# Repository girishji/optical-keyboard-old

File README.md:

# optical-keyboard

Keyboard PCB for Gateron optical switches (KiCad project).

- See [Optical Keyboard Design](https://girishji.github.io/jekyll/update/2022/08/17/optical-keyboard-design.html)
- There is a python script that is used for placing switches and laying out
  tracks. See also [KiCad 6 Python Scripting](https://girishji.github.io/)
- [QMK](https://github.com/girishji/qmk_firmware/tree/giri-optical-matrix/keyboards/opticalkb) code for this keyboard
- There is KiCad project for switch cutout plate under `switch-coutout` directory
- Part numbers for JLCPCB are embedded into symbols
- There is also a [single switch PCB](https://github.com/girishji/optical-amoeba)
- Another optical [keyboard](https://github.com/Dachtire/sok42) that might interest you
- Blackpill reference, including [pins to avoid](https://docs.qmk.fm/#/platformdev_blackpill_f411)

***

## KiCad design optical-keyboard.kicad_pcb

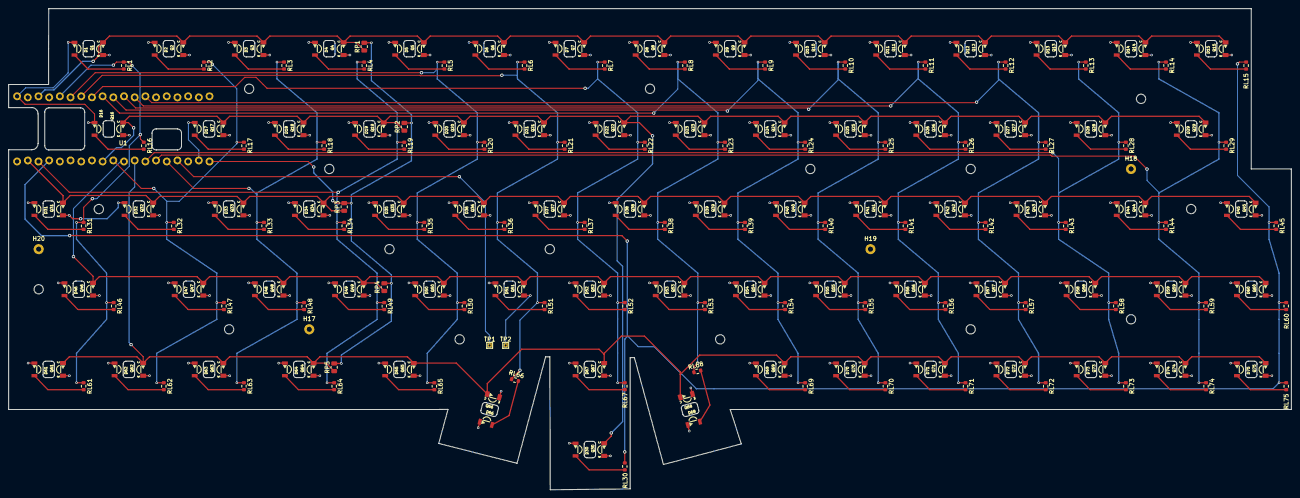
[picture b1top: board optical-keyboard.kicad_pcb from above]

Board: 2 copper layers, 304.8 x 114.3 mm, 328 parts (0 on the bottom side), 98 nets.

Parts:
D1, D2, D3, D4, D5, D6, D7, D8, D9, D10, D11, D12, D13, D14, D15, D16, D17, D18, D19, D20, D21, D22, D23, D24, D25, D26, D27, D28, D29, D30, D31, D32, D33, D34, D35, D36, D37, D38, D39, D40, D41, D42, D43, D44, D45, D46, D47, D48, D49, D50, D51, D52, D53, D54, D55, D56, D57, D58, D59, D60, D61, D62, D63, D64, D65, D66, D67, D68, D69, D70, D71, D72, D73, D74, D75: IR_LED; Everlight_IR_IR12-21C_TR8
H1, H2, H3, H4, H5, H6, H7, H8, H9, H10, H11, H12, H13, H14, H15, H16: MountingHole; MountingHole_2.2mm_M2_jlcpcb
H17, H18, H19, H20: MountingHole; TestPoint_Plated_Hole_D1.2mm
Q1, Q2, Q3, Q4, Q5, Q6, Q7, Q8, Q9, Q10, Q11, Q12, Q13, Q14, Q15, Q16, Q17, Q18, Q19, Q20, Q21, Q22, Q23, Q24, Q25, Q26, Q27, Q28, Q29, Q30, Q31, Q32, Q33, Q34, Q35, Q36, Q37, Q38, Q39, Q40, Q41, Q42, Q43, Q44, Q45, Q46, Q47, Q48, Q49, Q50, Q51, Q52, Q53, Q54, Q55, Q56, Q57, Q58, Q59, Q60, Q61, Q62, Q63, Q64, Q65, Q66, Q67, Q68, Q69, Q70, Q71, Q72, Q73, Q74, Q75: Q_Photo_NPN; Everlight_PT_PT12-21C_TR8
RL1, RL2, RL3, RL4, RL5, RL6, RL7, RL8, RL9, RL10, RL11, RL12, RL13, RL14, RL15, RL16, RL17, RL18, RL19, RL20, RL21, RL22, RL23, RL24, RL25, RL26, RL27, RL28, RL29, RL30, RL31, RL32, RL33, RL34, RL35, RL36, RL37, RL38, RL39, RL40, RL41, RL42, RL43, RL44, RL45, RL46, RL47, RL48, RL49, RL50, RL51, RL52, RL53, RL54, RL55, RL56, RL57, RL58, RL59, RL60, RL61, RL62, RL63, RL64, RL65, RL66, RL67, RL68, RL69, RL70, RL71, RL72, RL73, RL74, RL75: R_Led; R_0603_1608Metric
RP1, RP2, RP3, RP4, RP5: R_PT; R_0805_2012Metric
S1, S2, S3, S4, S5, S6, S7, S8, S9, S10, S11, S12, S13, S14, S15, S16, S17, S18, S19, S20, S21, S22, S23, S24, S25, S26, S27, S28, S29, S30, S31, S32, S33, S34, S35, S36, S37, S38, S39, S40, S41, S42, S43, S44, S45, S46, S47, S48, S49, S50, S51, S52, S53, S54, S55, S56, S57, S58, S59, S60, S61, S62, S63, S64, S65, S66, S67, S68, S69, S70, S71, S72, S73, S74, S75: Gateron_Optical; Gateron_Switch_Basic
TP1, TP2: TestPoint; TestPoint_THTPad_1.0x1.0mm_Drill0.5mm
U1: BlackPill_STLINK; BlackPill_STLINK2

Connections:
3v3: RP1.2, RP2.2, RP3.2, RP4.2, RP5.2, U1.20 (3V3)
/Capslock_Led: TP1.1, U1.17 (PB9)
/col1: RL1.1, RL16.1, RL31.1, RL46.1, RL61.1, U1.35 (PB1)
/col2: RL2.1, RL17.1, RL32.1, RL47.1, RL62.1, U1.11 (PB3)
/col3: RL3.1, RL18.1, RL33.1, RL48.1, RL63.1, U1.16 (PB8)
/col4: RL4.1, RL19.1, RL34.1, RL49.1, RL64.1, U1.4 (PB15)
/col5: RL5.1, RL20.1, RL35.1, RL50.1, RL65.1, U1.34 (PB0)
/col6: RL6.1, RL21.1, RL36.1, RL51.1, RL66.1, U1.33 (PA7)
/col7: RL7.1, RL22.1, RL37.1, RL52.1, RL67.1, U1.32 (PA6)
/col8: RL8.1, RL23.1, RL38.1, RL53.1, RL68.1, U1.31 (PA5)
/col9: RL9.1, RL24.1, RL39.1, RL54.1, RL69.1, U1.30 (PA4)
/col10: RL10.1, RL25.1, RL40.1, RL55.1, RL70.1, U1.29 (PA3)
/col11: RL11.1, RL26.1, RL41.1, RL56.1, RL71.1, U1.28 (PA2)
/col12: RL12.1, RL27.1, RL42.1, RL57.1, RL72.1, U1.27 (PA1)
/col13: RL13.1, RL28.1, RL43.1, RL58.1, RL73.1, U1.14 (PB6)
/col14: RL14.1, RL29.1, RL44.1, RL59.1, RL74.1, U1.15 (PB7)
/col15: RL15.1, RL30.1, RL45.1, RL60.1, RL75.1, U1.5 (PA8)
/row1: Q1.1 (C), Q2.1 (C), Q3.1 (C), Q4.1 (C), Q5.1 (C), Q6.1 (C), Q7.1 (C), Q8.1 (C), Q9.1 (C), Q10.1 (C), Q11.1 (C), Q12.1 (C), Q13.1 (C), Q14.1 (C), Q15.1 (C), RP1.1, U1.37 (PB10)
/row2: Q16.1 (C), Q17.1 (C), Q18.1 (C), Q19.1 (C), Q20.1 (C), Q21.1 (C), Q22.1 (C), Q23.1 (C), Q24.1 (C), Q25.1 (C), Q26.1 (C), Q27.1 (C), Q28.1 (C), Q29.1 (C), Q30.1 (C), RP2.1, U1.10 (PA15)
/row3: Q31.1 (C), Q32.1 (C), Q33.1 (C), Q34.1 (C), Q35.1 (C), Q36.1 (C), Q37.1 (C), Q38.1 (C), Q39.1 (C), Q40.1 (C), Q41.1 (C), Q42.1 (C), Q43.1 (C), Q44.1 (C), Q45.1 (C), RP3.1, U1.3 (PB14)
/row4: Q46.1 (C), Q47.1 (C), Q48.1 (C), Q49.1 (C), Q50.1 (C), Q51.1 (C), Q52.1 (C), Q53.1 (C), Q54.1 (C), Q55.1 (C), Q56.1 (C), Q57.1 (C), Q58.1 (C), Q59.1 (C), Q60.1 (C), RP4.1, U1.12 (PB4)
/row5: Q61.1 (C), Q62.1 (C), Q63.1 (C), Q64.1 (C), Q65.1 (C), Q66.1 (C), Q67.1 (C), Q68.1 (C), Q69.1 (C), Q70.1 (C), Q71.1 (C), Q72.1 (C), Q73.1 (C), Q74.1 (C), Q75.1 (C), RP5.1, U1.13 (PB5)
GND: D1.1 (K), D2.1 (K), D3.1 (K), D4.1 (K), D5.1 (K), D6.1 (K), D7.1 (K), D8.1 (K), D9.1 (K), D10.1 (K), D11.1 (K), D12.1 (K), D13.1 (K), D14.1 (K), D15.1 (K), D16.1 (K), D17.1 (K), D18.1 (K), D19.1 (K), D20.1 (K), D21.1 (K), D22.1 (K), D23.1 (K), D24.1 (K), D25.1 (K), D26.1 (K), D27.1 (K), D28.1 (K), D29.1 (K), D30.1 (K), D31.1 (K), D32.1 (K), D33.1 (K), D34.1 (K), D35.1 (K), D36.1 (K), D37.1 (K), D38.1 (K), D39.1 (K), D40.1 (K), D41.1 (K), D42.1 (K), D43.1 (K), D44.1 (K), D45.1 (K), D46.1 (K), D47.1 (K), D48.1 (K), D49.1 (K), D50.1 (K), D51.1 (K), D52.1 (K), D53.1 (K), D54.1 (K), D55.1 (K), D56.1 (K), D57.1 (K), D58.1 (K), D59.1 (K), D60.1 (K), D61.1 (K), D62.1 (K), D63.1 (K), D64.1 (K), D65.1 (K), D66.1 (K), D67.1 (K), D68.1 (K), D69.1 (K), D70.1 (K), D71.1 (K), D72.1 (K), D73.1 (K), D74.1 (K), D75.1 (K), Q1.2 (E), Q2.2 (E), Q3.2 (E), Q4.2 (E), Q5.2 (E), Q6.2 (E), Q7.2 (E), Q8.2 (E), Q9.2 (E), Q10.2 (E), Q11.2 (E), Q12.2 (E), Q13.2 (E), Q14.2 (E), Q15.2 (E), Q16.2 (E), Q17.2 (E), Q18.2 (E), Q19.2 (E), Q20.2 (E), Q21.2 (E), Q22.2 (E), Q23.2 (E), Q24.2 (E), Q25.2 (E), Q26.2 (E), Q27.2 (E), Q28.2 (E), Q29.2 (E), Q30.2 (E), Q31.2 (E), Q32.2 (E), Q33.2 (E), Q34.2 (E), Q35.2 (E), Q36.2 (E), Q37.2 (E), Q38.2 (E), Q39.2 (E), Q40.2 (E), Q41.2 (E), Q42.2 (E), Q43.2 (E), Q44.2 (E), Q45.2 (E), Q46.2 (E), Q47.2 (E), Q48.2 (E), Q49.2 (E), Q50.2 (E), Q51.2 (E), Q52.2 (E), Q53.2 (E), Q54.2 (E), Q55.2 (E), Q56.2 (E), Q57.2 (E), Q58.2 (E), Q59.2 (E), Q60.2 (E), Q61.2 (E), Q62.2 (E), Q63.2 (E), Q64.2 (E), Q65.2 (E), Q66.2 (E), Q67.2 (E), Q68.2 (E), Q69.2 (E), Q70.2 (E), Q71.2 (E), Q72.2 (E), Q73.2 (E), Q74.2 (E), Q75.2 (E), TP2.1, U1.19 (GND), U1.39 (GND)
unnamed: D1.2 (A), RL1.2
unnamed: D2.2 (A), RL2.2
unnamed: D3.2 (A), RL3.2
unnamed: D4.2 (A), RL4.2
unnamed: D5.2 (A), RL5.2
unnamed: D6.2 (A), RL6.2
unnamed: D7.2 (A), RL7.2
unnamed: D8.2 (A), RL8.2
unnamed: D9.2 (A), RL9.2
unnamed: D10.2 (A), RL10.2
unnamed: D11.2 (A), RL11.2
unnamed: D12.2 (A), RL12.2
unnamed: D13.2 (A), RL13.2
unnamed: D14.2 (A), RL14.2
unnamed: D15.2 (A), RL15.2
unnamed: D16.2 (A), RL16.2
unnamed: D17.2 (A), RL17.2
unnamed: D18.2 (A), RL18.2
unnamed: D19.2 (A), RL19.2
unnamed: D20.2 (A), RL20.2
unnamed: D21.2 (A), RL21.2
unnamed: D22.2 (A), RL22.2
unnamed: D23.2 (A), RL23.2
unnamed: D24.2 (A), RL24.2
unnamed: D25.2 (A), RL25.2
unnamed: D26.2 (A), RL26.2
unnamed: D27.2 (A), RL27.2
unnamed: D28.2 (A), RL28.2
unnamed: D29.2 (A), RL29.2
unnamed: D30.2 (A), RL30.2
unnamed: D31.2 (A), RL31.2
unnamed: D32.2 (A), RL32.2
unnamed: D33.2 (A), RL33.2
unnamed: D34.2 (A), RL34.2
unnamed: D35.2 (A), RL35.2
unnamed: D36.2 (A), RL36.2
unnamed: D37.2 (A), RL37.2
unnamed: D38.2 (A), RL38.2
unnamed: D39.2 (A), RL39.2
unnamed: D40.2 (A), RL40.2
unnamed: D41.2 (A), RL41.2
unnamed: D42.2 (A), RL42.2
unnamed: D43.2 (A), RL43.2
unnamed: D44.2 (A), RL44.2
unnamed: D45.2 (A), RL45.2
unnamed: D46.2 (A), RL46.2
unnamed: D47.2 (A), RL47.2
unnamed: D48.2 (A), RL48.2
unnamed: D49.2 (A), RL49.2
unnamed: D50.2 (A), RL50.2
unnamed: D51.2 (A), RL51.2
unnamed: D52.2 (A), RL52.2
unnamed: D53.2 (A), RL53.2
unnamed: D54.2 (A), RL54.2
unnamed: D55.2 (A), RL55.2
unnamed: D56.2 (A), RL56.2
unnamed: D57.2 (A), RL57.2
unnamed: D58.2 (A), RL58.2
unnamed: D59.2 (A), RL59.2
unnamed: D60.2 (A), RL60.2
unnamed: D61.2 (A), RL61.2
unnamed: D62.2 (A), RL62.2
unnamed: D63.2 (A), RL63.2
unnamed: D64.2 (A), RL64.2
unnamed: D65.2 (A), RL65.2
unnamed: D66.2 (A), RL66.2
unnamed: D67.2 (A), RL67.2
unnamed: D68.2 (A), RL68.2
unnamed: D69.2 (A), RL69.2
unnamed: D70.2 (A), RL70.2
unnamed: D71.2 (A), RL71.2
unnamed: D72.2 (A), RL72.2
unnamed: D73.2 (A), RL73.2
unnamed: D74.2 (A), RL74.2
unnamed: D75.2 (A), RL75.2

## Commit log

2022-07-19 first commit
    A .gitignore
    A fp-lib-table
    A optical-keyboard.kicad_pcb
    A optical-keyboard.kicad_prl
    A optical-keyboard.kicad_pro
    A optical-keyboard.kicad_sch
2022-07-20 updated pcb
    M optical-keyboard.kicad_pcb
    M optical-keyboard.kicad_pro
    M optical-keyboard.kicad_sch
    M placefp.py
    M switch.kicad_sch
2022-07-20 update schematic
    M optical-keyboard.kicad_sch
    M switch.kicad_sch
2022-07-21 update footprint
    M optical-keyboard.kicad_pcb
2022-07-30 Added description
    M README.md
    M optical-keyboard.kicad_pro
    M switch-cutout/switch-cutout.kicad_pro
    A switch-cutout/sym-lib-table
2022-07-31 Fixed bug in symbols by removing arrows
    M optical-keyboard.kicad_sch
    M switch.kicad_sch
2022-07-31 Fixed pic
    M README.md
2022-07-31 Update
    M README.md
2022-08-01 Add separate power source for PTs
    Sharing input pin b/w pt and led requires a diode, and diode
    slows down the response time of pt considerably
    M optical-keyboard.kicad_pcb
    M optical-keyboard.kicad_prl
    M optical-keyboard.kicad_sch
    M placefp.py
2022-08-01 Add footprints library
    A OpticalSymbols_Library.kicad_sym
    A Optical_Parts.pretty/BlackPill_STLINK.kicad_mod
    A Optical_Parts.pretty/BlackPill_STLINK2.kicad_mod
    A Optical_Parts.pretty/Everlight_IR_IR12-21C_TR8.kicad_mod
    A Optical_Parts.pretty/Everlight_PT_PT12-21C_TR8.kicad_mod
    A Optical_Parts.pretty/Gateron_Optical_Switch.kicad_mod
2022-08-03 Fix footprint hole size
    Cutouts should be 14x14 mm, not 13.8mm square; This fits
    both gateron and keychron optical switches
    M Optical_Parts.pretty/Switch_Cutout.kicad_mod
    M Optical_Parts.pretty/Switch_Cutout_1.25u.kicad_mod
    M Optical_Parts.pretty/Switch_Cutout_1.5u.kicad_mod
    M Optical_Parts.pretty/Switch_Cutout_1.75u.kicad_mod
2022-08-19 update readme
    M README.md
    M switch-cutout/switch-cutout.kicad_prl
2022-08-19 readme
    M README.md
